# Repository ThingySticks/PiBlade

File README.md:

# Pi Blade

A 2U high "Blade" center for the Raspberry Pi (or many).

Design inspired by (1) which was inspired by (2) to use the DAP Audio 2 HE Rackblende f. Modulsystem 10 Segmente MP-1 (3), a 2U rack mount system with 10x 44mm wide panels.

## Rack Enclosure

This is the main intended enclosure, if the DAP Audio one isn't available this might be useful, hopefully some add-on bits for the modulsystem as well.

This is made of a number of parts.

* PiRackfrontPanel.svg/dxf - this is a 2U high laser cuttable version of the DAP Audio 2 HE Rackblende f. Modulsystem 10 Segmente MP-1. If you can't get the rack or don't want to wait (or don't mind an acrylic version this might work...

* PiRackRearSide.stl - a 3D printable 1/3 enclosure (side panel). 
** Intended to to around the back of the laser cut panel (not sure how well it will work with the proper rack).
** Print 2x of these, one for each side, then the middle section, these screw to the back of the laser cut acrylic.

## Standalone Enclosure

When getting the Pi's ready you probably don't want to put them in the rack, so this little barn style enclosure allows the blade to be screwed into it to hold it. The Fusion 360 design is scalable to allow multiple units.

* PiBarn-1.stl - 1 blade high
* PiBarn-3.stl - 3 blades high

# Front Panels

These consist of 3D printed panels () and are screwed to the blades.

* McPiFace - is a PCB panel, this can be sent to a fab house such as OSH Park to nicly make the panels.
* Panels from https://www.thingiverse.com/thing:2759317 can also be used and mounted onto the "Blades"

# Blades

These are the carrier frames for the Pi's. Compatible with https://www.thingiverse.com/thing:2759317

* PiRackPiBase.stl - this is the basic Pi blade base.
* PiRackPiLongBase.stl - this will hold 2x Pi's back to back, or HAT base from the Pi Sandwich https://github.com/ThingySticks/PiHatSandwich
** Obviously network connectivity is an issue for the second rear pi when mounting 2x Pi's.

## References

(1) https://www.thingiverse.com/thing:2759317
(2) https://www.thingiverse.com/thing:1793758
(3) https://www.musicstore.de/en_GB/GBP/DAP-Audio-2-HE-Rackblende-f-Modulsystem-10-Segmente-MP-1/art-PAH0017160-000

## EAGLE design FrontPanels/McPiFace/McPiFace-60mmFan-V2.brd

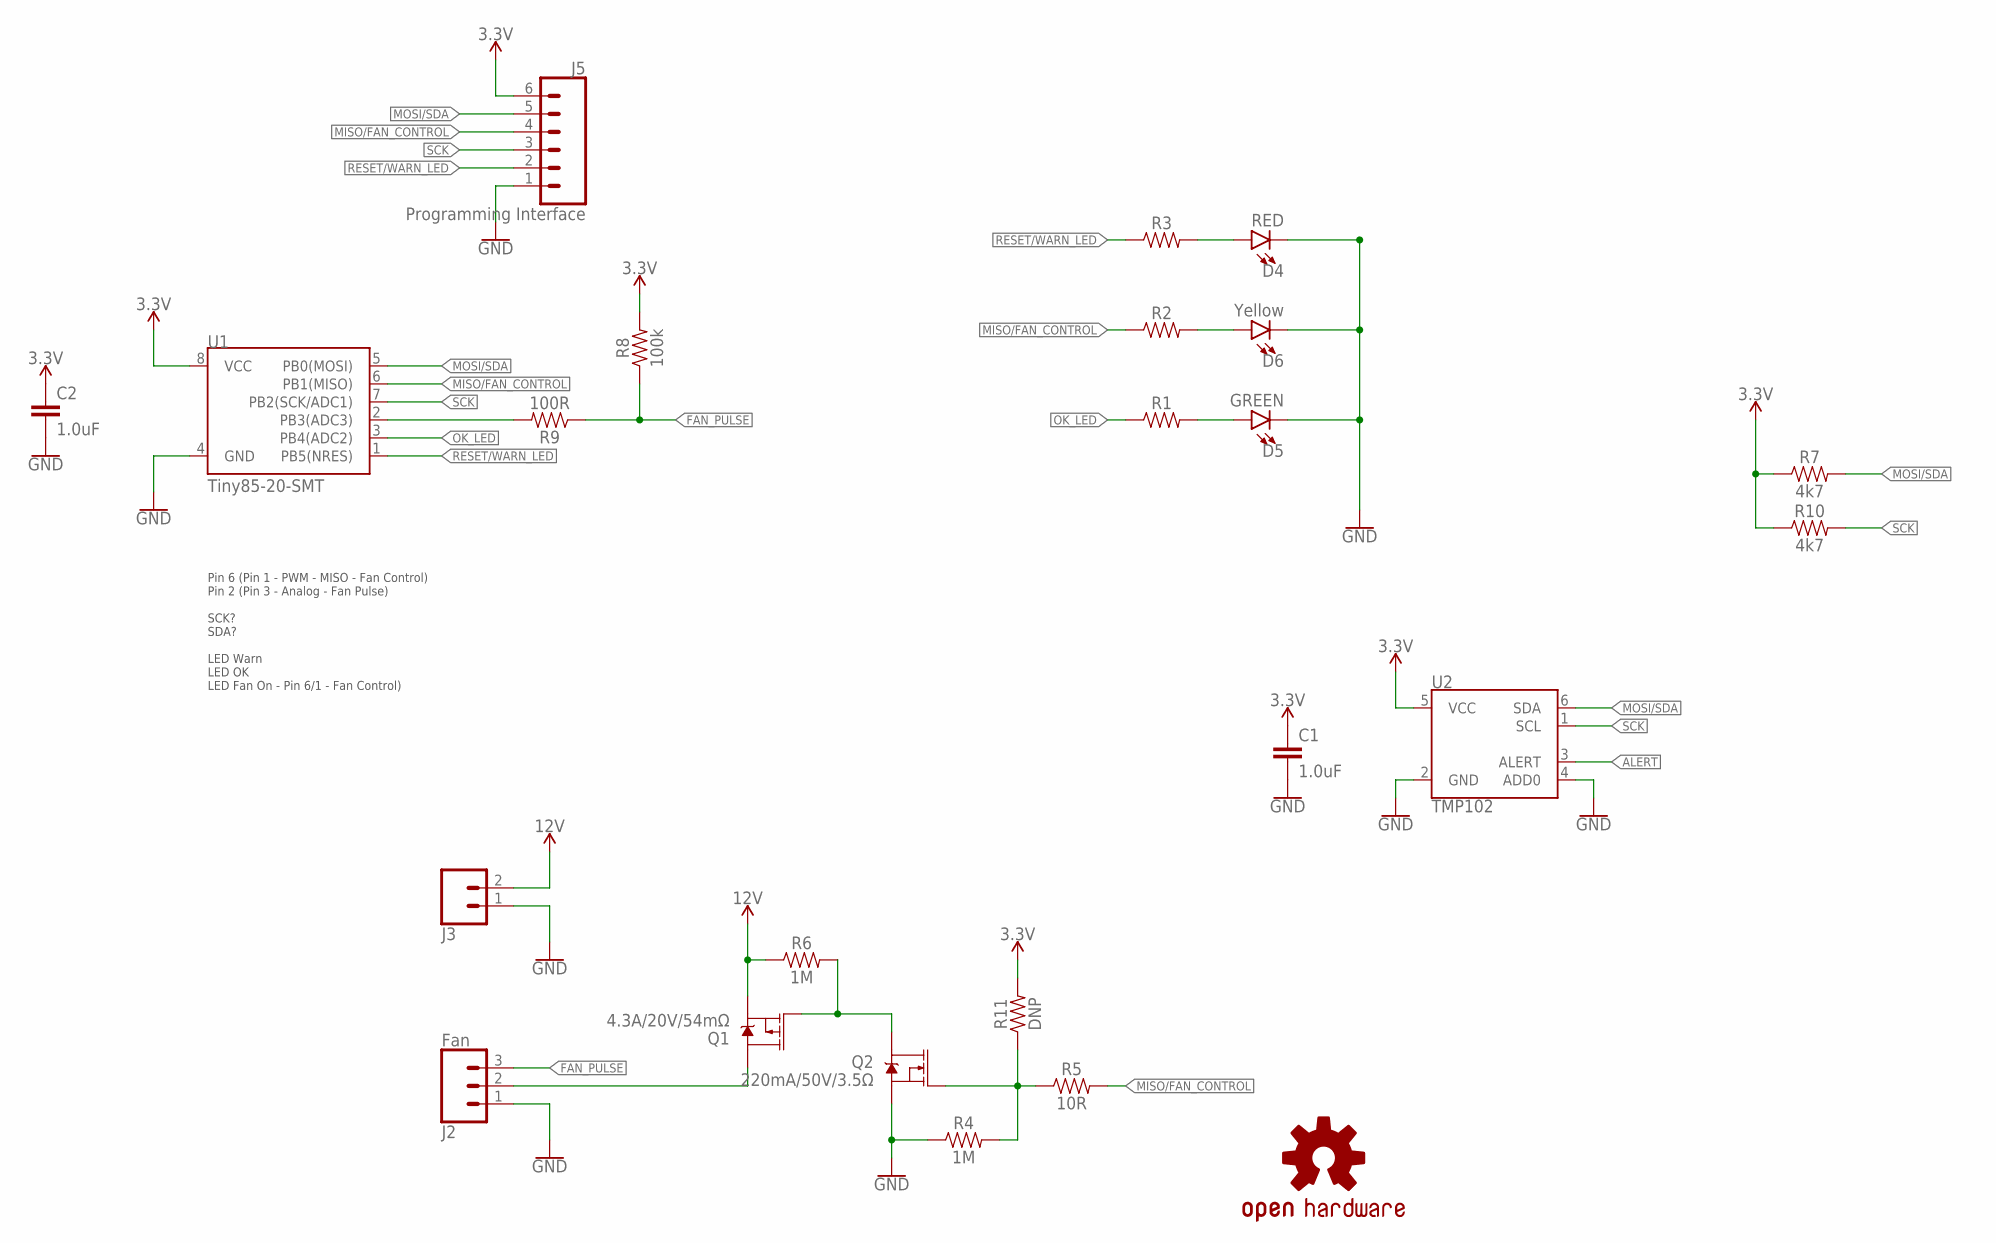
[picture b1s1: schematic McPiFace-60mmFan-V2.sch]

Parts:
C1, C2: 1.0uF; 0805
D4: RED; LED-1206
D5: GREEN; LED-1206
D6: Yellow; LED-1206
J2: Fan; JST-3-SMD; FARNELL 9492623
J3: CONN_02-JST-2MM-SMT; JST-2-SMD; FARNELL 9492615
J5: Programming Interface; 1X06-1MM
LOGO1: OSHW-LOGOL; OSHW-LOGO-L
Q1: 4.3A/20V/54mΩ; SOT23-3
Q2: 220mA/50V/3.5Ω; SOT23-3
R1, R2, R3: 1206
R4, R6: 1M; 0805
R5: 10R; 0805
R7, R10: 4k7; 0805
R8: 100k; 0805
R9: 100R; 0805
R11: DNP; 0805
U1: Tiny85-20-SMT; SO08-EIAJ
U2: TMP102; SOT563

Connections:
3.3V: C1.1, C2.1, J5.6, R7.1, R8.2, R10.1, R11.2, U1.8 (VCC), U2.5 (VCC)
12V: J3.2 (1), Q1.2 (S), R6.1
ALERT: U2.3 (ALERT)
FAN_PULSE: J2.3 (1), R8.1, R9.1
GND: C1.2, C2.2, D4.C, D5.C, D6.C, J2.1 (3), J3.1 (2), J5.1, Q2.2 (S), R4.1, U1.4 (GND), U2.2 (GND), U2.4 (ADD0)
MISO/FAN_CONTROL: J5.4, R2.1, R5.2, U1.6 (PB1(MISO))
MOSI/SDA: J5.5, R7.2, U1.5 (PB0(MOSI)), U2.6 (SDA)
unnamed: R9.2, U1.2 (PB3(ADC3))
unnamed: D4.A, R3.2
unnamed: D6.A, R2.2
unnamed: D5.A, R1.2
unnamed: J2.2, Q1.3 (D)
unnamed: Q1.1 (G), Q2.3 (D), R6.2
unnamed: Q2.1 (G), R4.2, R5.1, R11.1
OK_LED: R1.1, U1.3 (PB4(ADC2))
RESET/WARN_LED: J5.2, R3.1, U1.1 (PB5(NRES))
SCK: J5.3, R10.2, U1.7 (PB2(SCK/ADC1)), U2.1 (SCL)

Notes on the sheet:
Pin 6 (Pin 1 - PWM - MISO - Fan Control) Pin 2 (Pin 3 - Analog - Fan Pulse) SCK? SDA? LED Warn LED OK LED Fan On - Pin 6/1 - Fan Control)

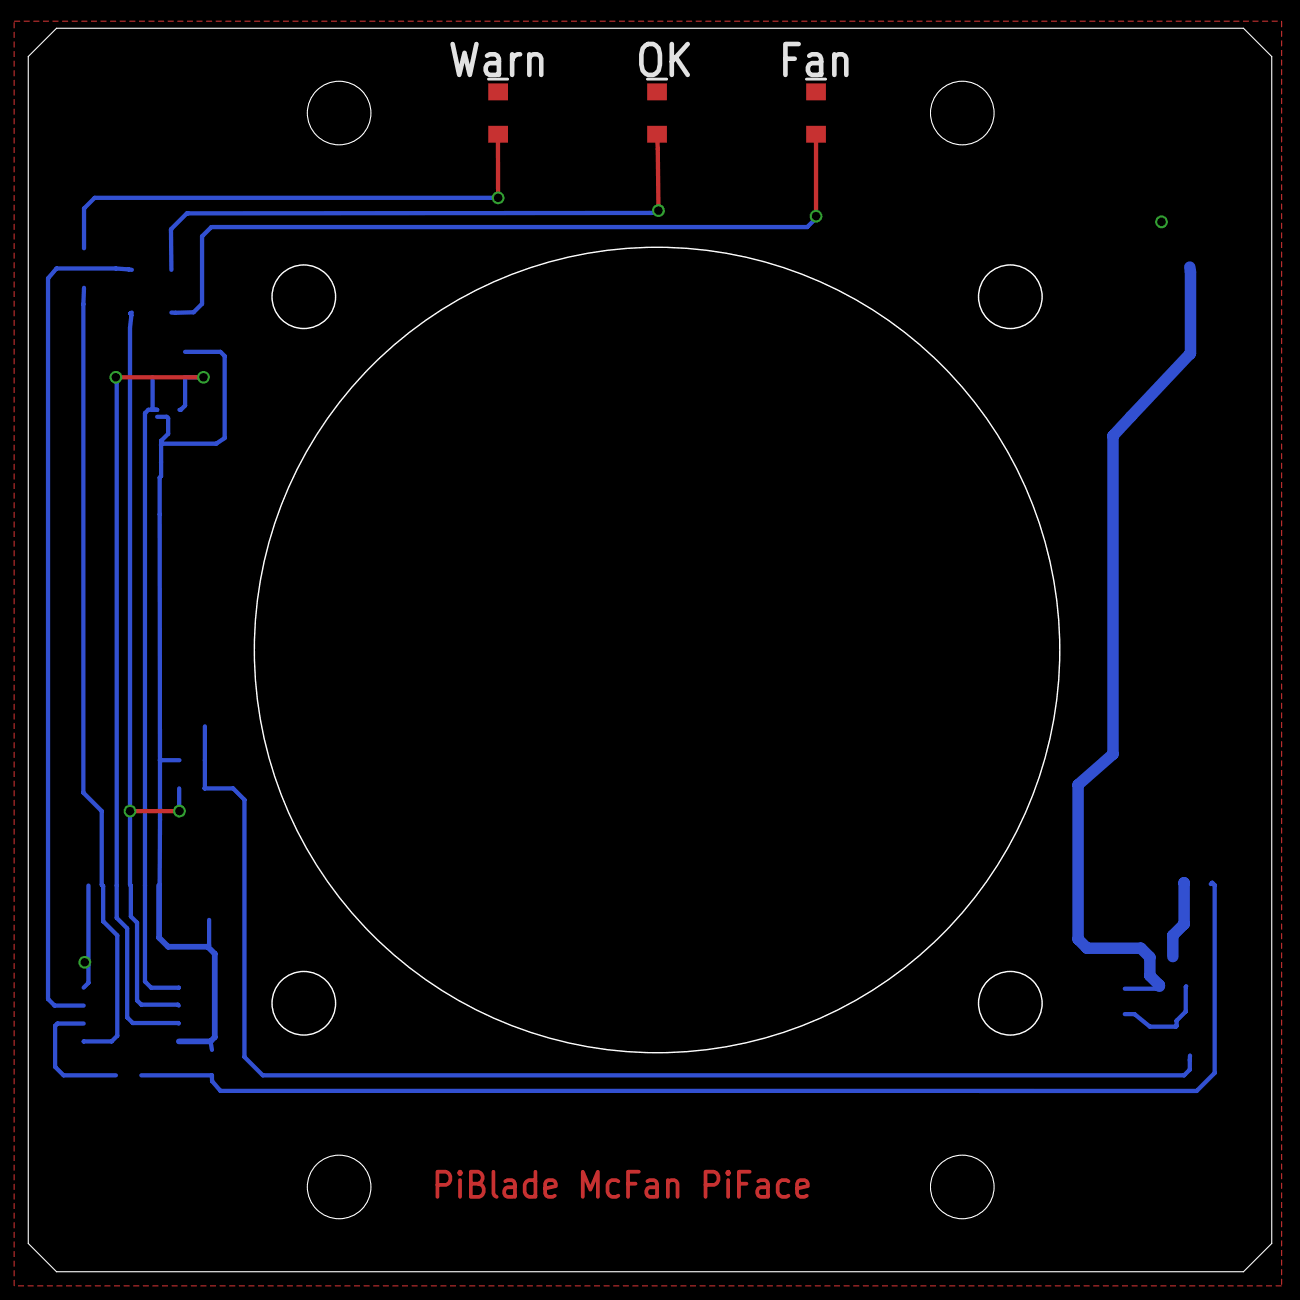
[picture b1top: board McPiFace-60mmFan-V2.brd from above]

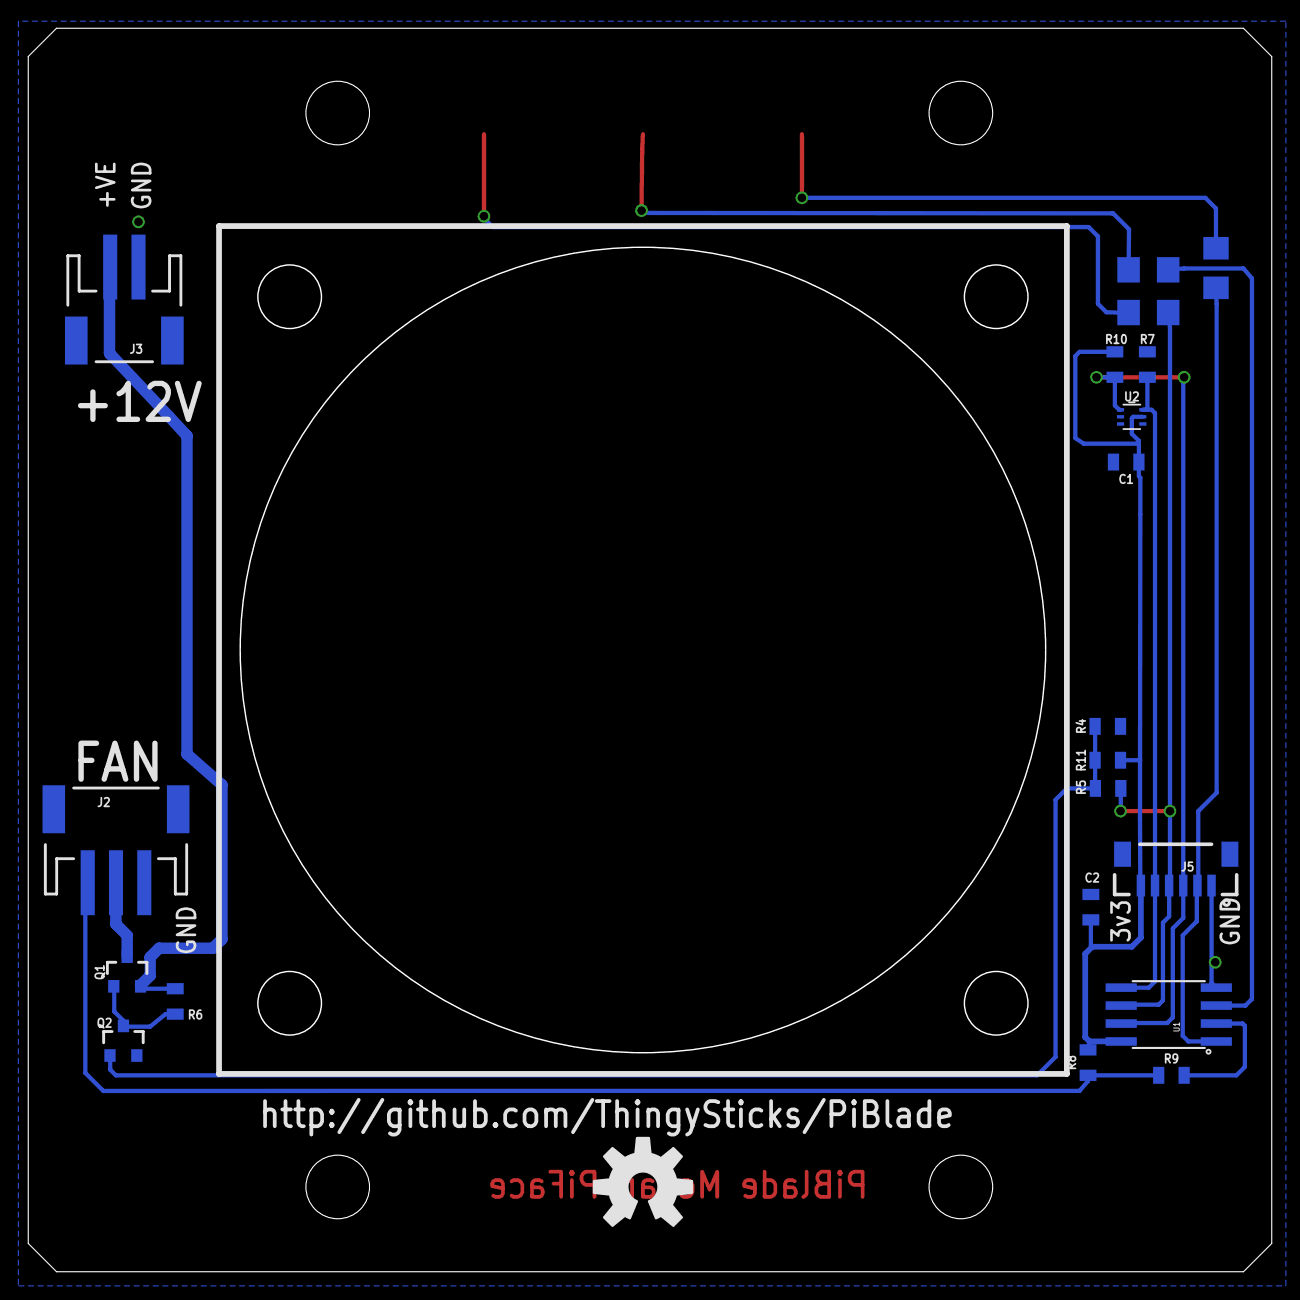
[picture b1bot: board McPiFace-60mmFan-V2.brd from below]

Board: 2 copper layers, 88.0 x 88.0 mm, 24 parts (21 on the bottom side), 16 nets.

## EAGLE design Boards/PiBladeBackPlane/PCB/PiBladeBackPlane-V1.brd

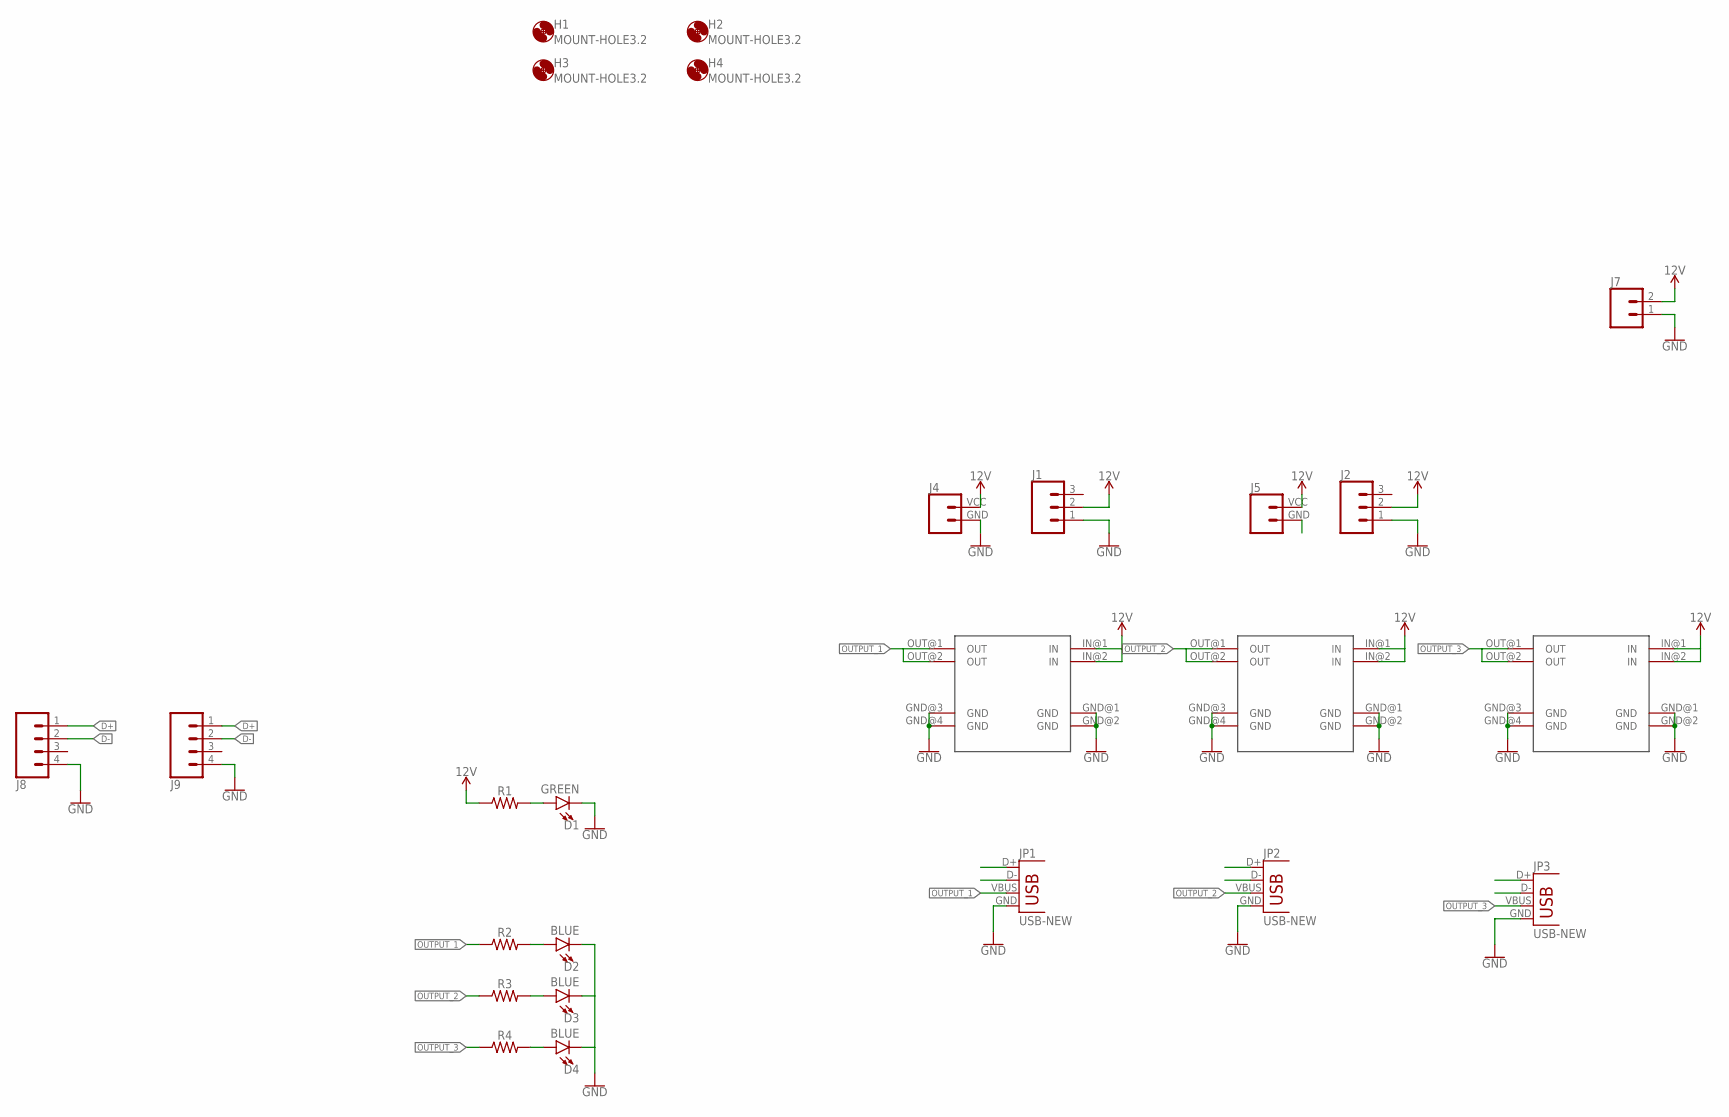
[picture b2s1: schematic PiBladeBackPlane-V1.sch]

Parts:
D1: GREEN; LED-1206
D2, D3, D4: BLUE; LED-1206
H1, H2, H3, H4: MOUNT-HOLE3.2; 3,2
J1, J2: CONN_03POLAR; MOLEX-1X3
J4, J5: CONN_024UCON-15767; JST-2-SMD-VERT
J7: CONN_025MM; SCREWTERMINAL-5MM-2
J8, J9: CONN_04JST-PTH-VERT; JST-4-PTH-VERT
JP1, JP2, JP3: USB-NEW; USB-A-VERTICAL
R1, R2, R3, R4: 1206
U$1, U$2, U$3: MINI-BUCK-MODULE-3A

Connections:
12V: J1.2, J2.2, J4.VCC (2), J5.VCC (2), J7.2, R1.1, U$1.IN@1 (IN), U$1.IN@2 (IN), U$2.IN@1 (IN), U$2.IN@2 (IN), U$3.IN@1 (IN), U$3.IN@2 (IN)
D+: J8.1, J9.1, JP1.D+, JP2.D+, JP3.D+
D-: J8.2, J9.2, JP1.D-, JP2.D-, JP3.D-
GND: D1.C, D2.C, D3.C, D4.C, J1.1, J2.1, J4.GND (1), J7.1, J8.4, JP1.GND, JP2.GND, JP3.GND, U$1.GND@1 (GND), U$1.GND@2 (GND), U$1.GND@3 (GND), U$1.GND@4 (GND), U$2.GND@1 (GND), U$2.GND@2 (GND), U$2.GND@3 (GND), U$2.GND@4 (GND), U$3.GND@1 (GND), U$3.GND@2 (GND), U$3.GND@3 (GND), U$3.GND@4 (GND)
unnamed: D1.A, R1.2
unnamed: D4.A, R4.2
unnamed: D2.A, R2.2
unnamed: D3.A, R3.2
OUTPUT_1: JP1.VBUS, R2.1, U$1.OUT@1 (OUT), U$1.OUT@2 (OUT)
OUTPUT_2: JP2.VBUS, R3.1, U$2.OUT@1 (OUT), U$2.OUT@2 (OUT)
OUTPUT_3: JP3.VBUS, R4.1, U$3.OUT@1 (OUT), U$3.OUT@2 (OUT)

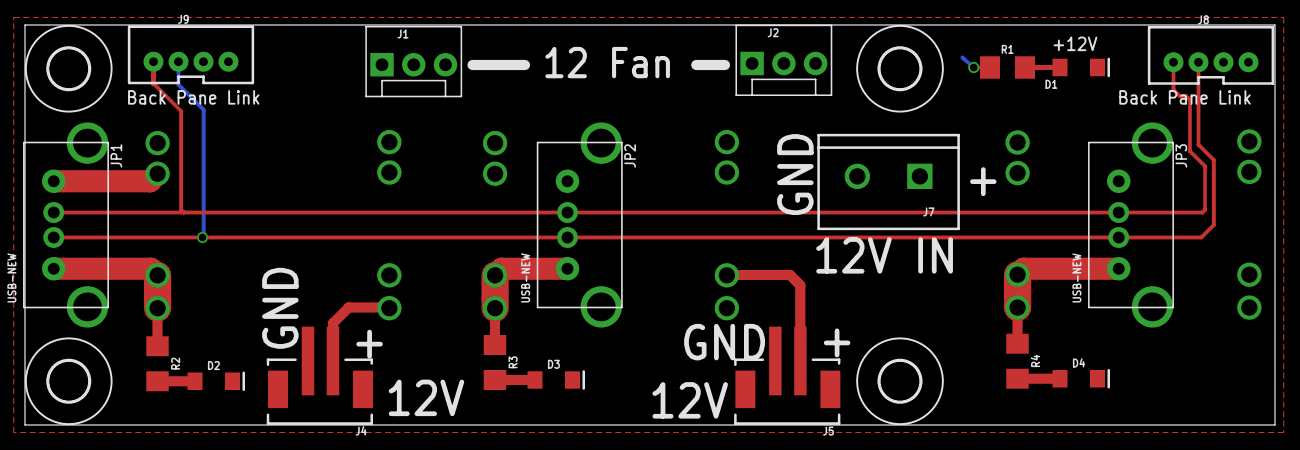
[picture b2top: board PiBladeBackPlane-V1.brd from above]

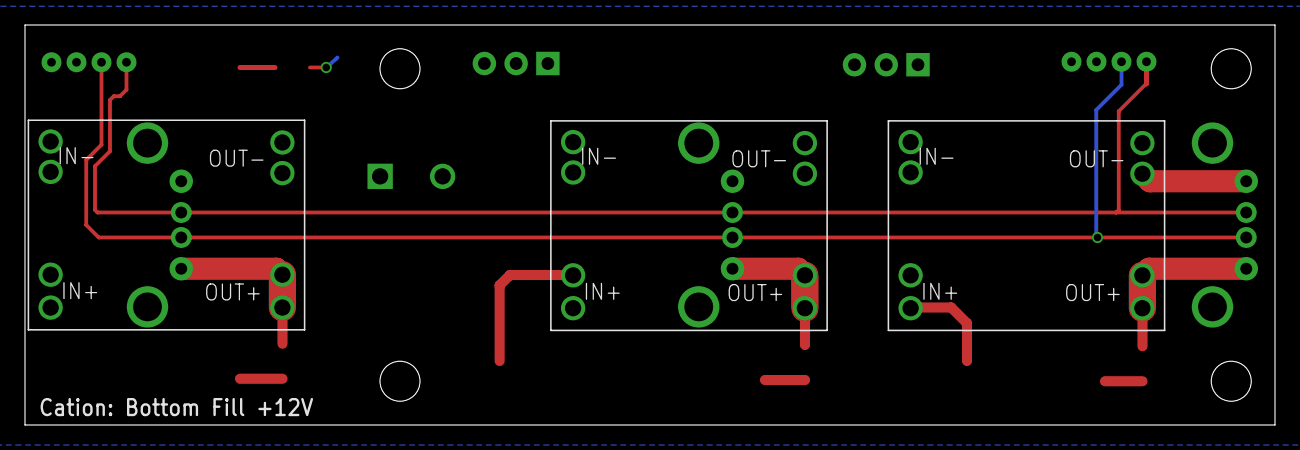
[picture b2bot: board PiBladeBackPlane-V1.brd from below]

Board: 2 copper layers, 100.0 x 32.0 mm, 25 parts (6 on the bottom side), 11 nets.

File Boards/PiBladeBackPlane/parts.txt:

Partlist

Exported from PiBladeBackPlane-V1.brd at 25/01/2019 11:45

EAGLE Version 7.4.0 Copyright (c) 1988-2015 CadSoft

Assembly variant: 

Part     Value               Package             Library             Position (mm)         Orientation

D1       GREEN               LED-1206            SparkFun-LED        (84.3 28.6)           R0
D2       BLUE                LED-1206            SparkFun-LED        (15.1 3.5)            R0
D3       BLUE                LED-1206            SparkFun-LED        (42.3 3.6)            R0
D4       BLUE                LED-1206            SparkFun-LED        (84.3 3.7)            R0
J1                           MOLEX-1X3           SparkFun-Connectors (28.56 28.82)         R0
J2                           MOLEX-1X3           SparkFun-Connectors (58.17 28.92)         R0
J4                           JST-2-SMD-VERT      SparkFun-Connectors (23.64 3.12)          R180
J5                           JST-2-SMD-VERT      SparkFun-Connectors (61.03 3.12)          R180
J7                           SCREWTERMINAL-5MM-2 SparkFun-Connectors (71.59 19.89)         R180
J8                           JST-4-PTH-VERT      SparkFun-Connectors (94.88 29.57)         R0
J9                           JST-4-PTH-VERT      SparkFun-Connectors (13.28 29.61)         R0
JP1      USB-NEW             USB-A-VERTICAL      Tinamous            (5 16)                MR0
JP2      USB-NEW             USB-A-VERTICAL      Tinamous            (46.1 16)             MR0
JP3      USB-NEW             USB-A-VERTICAL      Tinamous            (90.2 16)             MR0
R1                           1206                SparkFun-Resistors  (78.6 28.6)           R0
R2                           1206                SparkFun-Resistors  (10.6 4.9)            R270
R3                           1206                SparkFun-Resistors  (37.6 5)              R270
R4                           1206                SparkFun-Resistors  (79.4 5.1)            R270
U$1      MINI-BUCK-MODULE-3A MINI-BUCK-MODULE-3A Tinamous            (8.83 24.33)          MR180
U$2      MINI-BUCK-MODULE-3A MINI-BUCK-MODULE-3A Tinamous            (35.83 24.33)         MR180
U$3      MINI-BUCK-MODULE-3A MINI-BUCK-MODULE-3A Tinamous            (77.63 24.38)         MR180

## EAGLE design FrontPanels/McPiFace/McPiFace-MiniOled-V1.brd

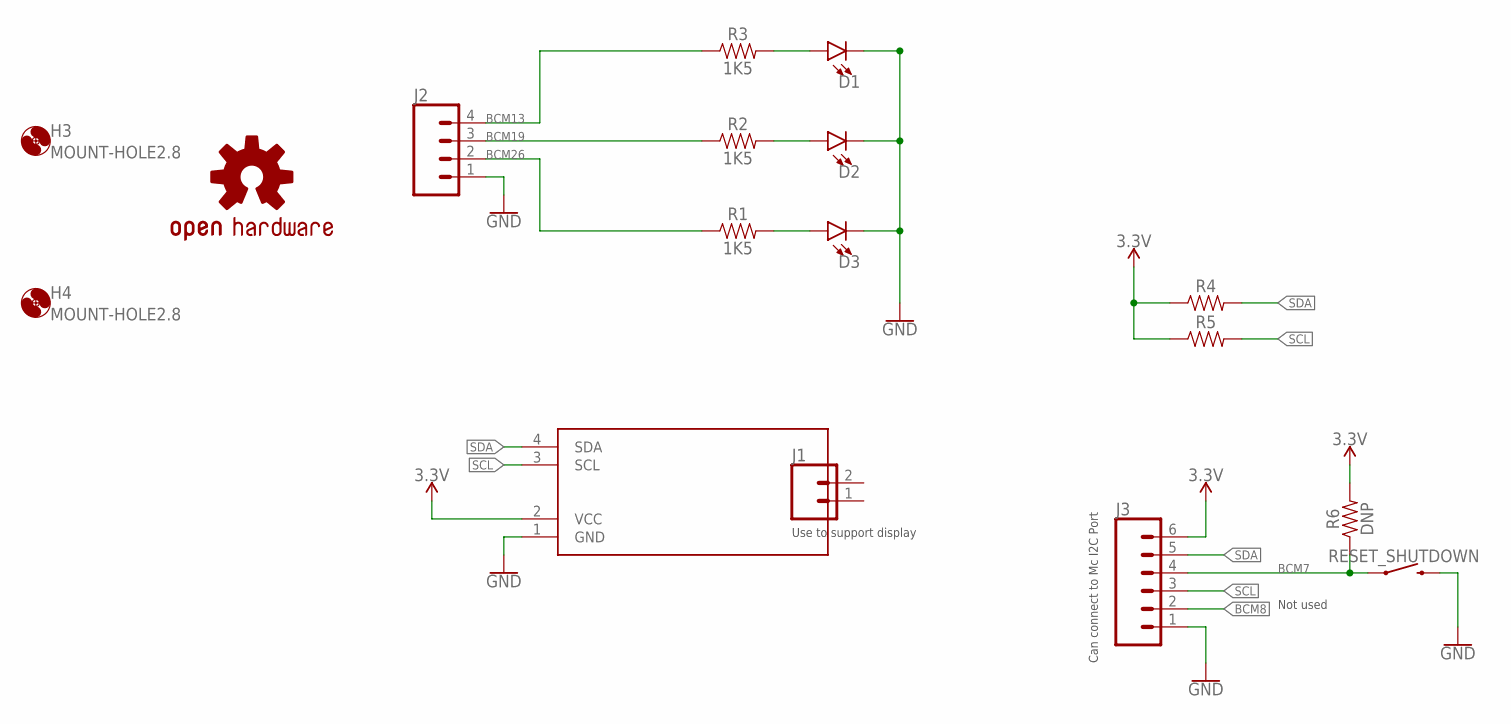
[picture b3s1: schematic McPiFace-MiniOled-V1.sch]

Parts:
D1, D2, D3: LED1206-BOTTOM-1.6MM; LED-1206-BOTTOM-1.6MM
DISPLAY: DISPLAY0.91_INCH_DISPLAY; I2C_DISPLAY_0.91_INCH
H3, H4: MOUNT-HOLE2.8; 2,8
J1: CONN_021X02_NO_SILK; 1X02_NO_SILK
J2: CONN_04SMD2; 1X04_1MM_RA
J3: CONN_06SMD-1MM; 1X06-1MM
LOGO1: OSHW-LOGOL; OSHW-LOGO-L
R1, R2, R3: 1K5; 0805
R4, R5: 0805
R6: DNP; 0805
RESET_SHUTDOWN: Reset/Powerdown; TACTILE_SWITCH_PTH_6.0MM_NO_TOP_RESIST

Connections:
3.3V: DISPLAY.2 (VCC), J3.6, R4.1, R5.1, R6.2
BCM7: J3.4, R6.1, RESET_SHUTDOWN.1
BCM8: J3.2
BCM13: J2.4, R3.1
BCM19: J2.3, R2.1
BCM26: J2.2, R1.1
GND: D1.C, D2.C, D3.C, DISPLAY.1 (GND), J2.1, J3.1, RESET_SHUTDOWN.3 (2)
unnamed: D3.A, R1.2
unnamed: D1.A, R3.2
unnamed: D2.A, R2.2
SCL: DISPLAY.3 (SCL), J3.3, R5.2
SDA: DISPLAY.4 (SDA), J3.5, R4.2

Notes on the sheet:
Use to support display
Not used
Can connect to Mc I2C Port

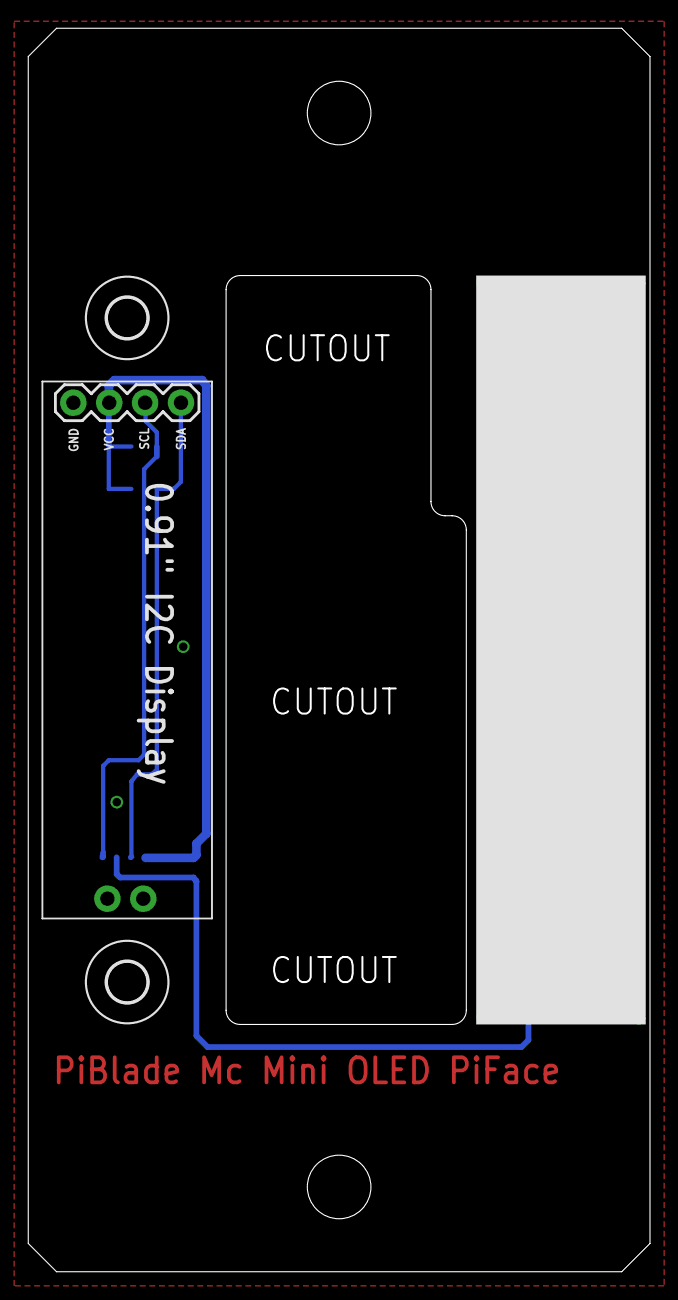
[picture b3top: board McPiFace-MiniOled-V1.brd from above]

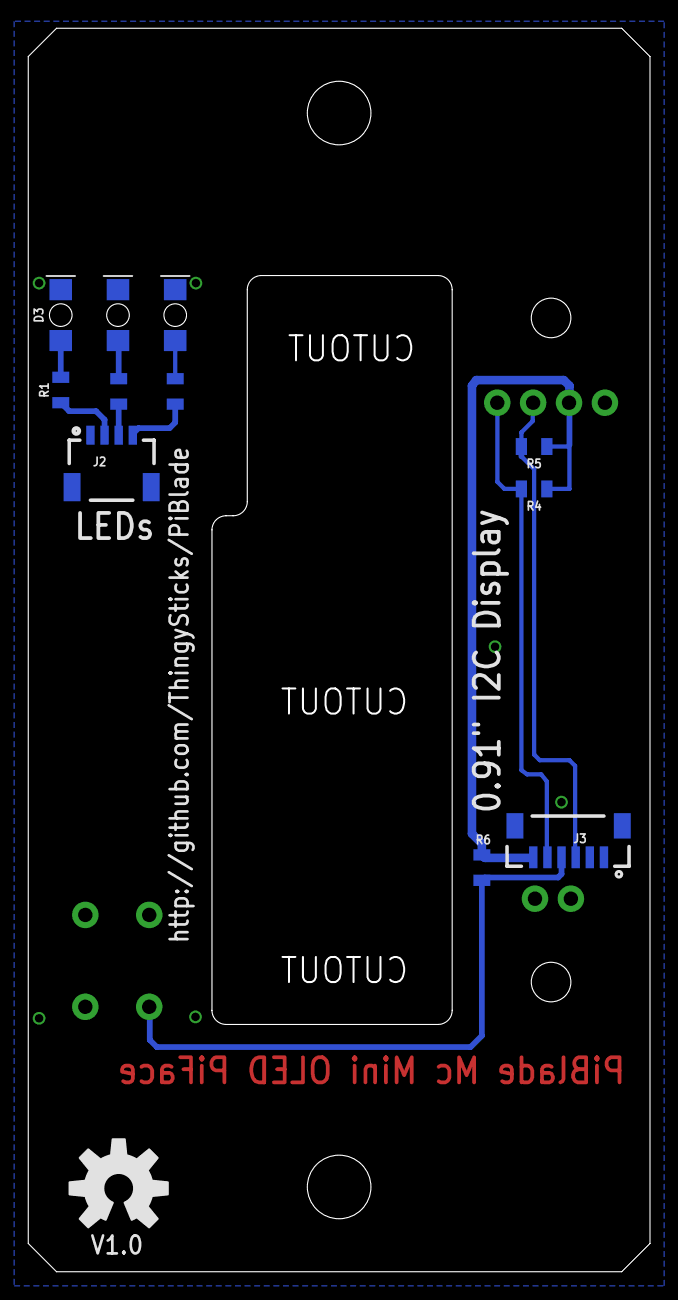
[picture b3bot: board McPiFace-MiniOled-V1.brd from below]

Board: 2 copper layers, 44.0 x 88.0 mm, 17 parts (12 on the bottom side), 11 nets.

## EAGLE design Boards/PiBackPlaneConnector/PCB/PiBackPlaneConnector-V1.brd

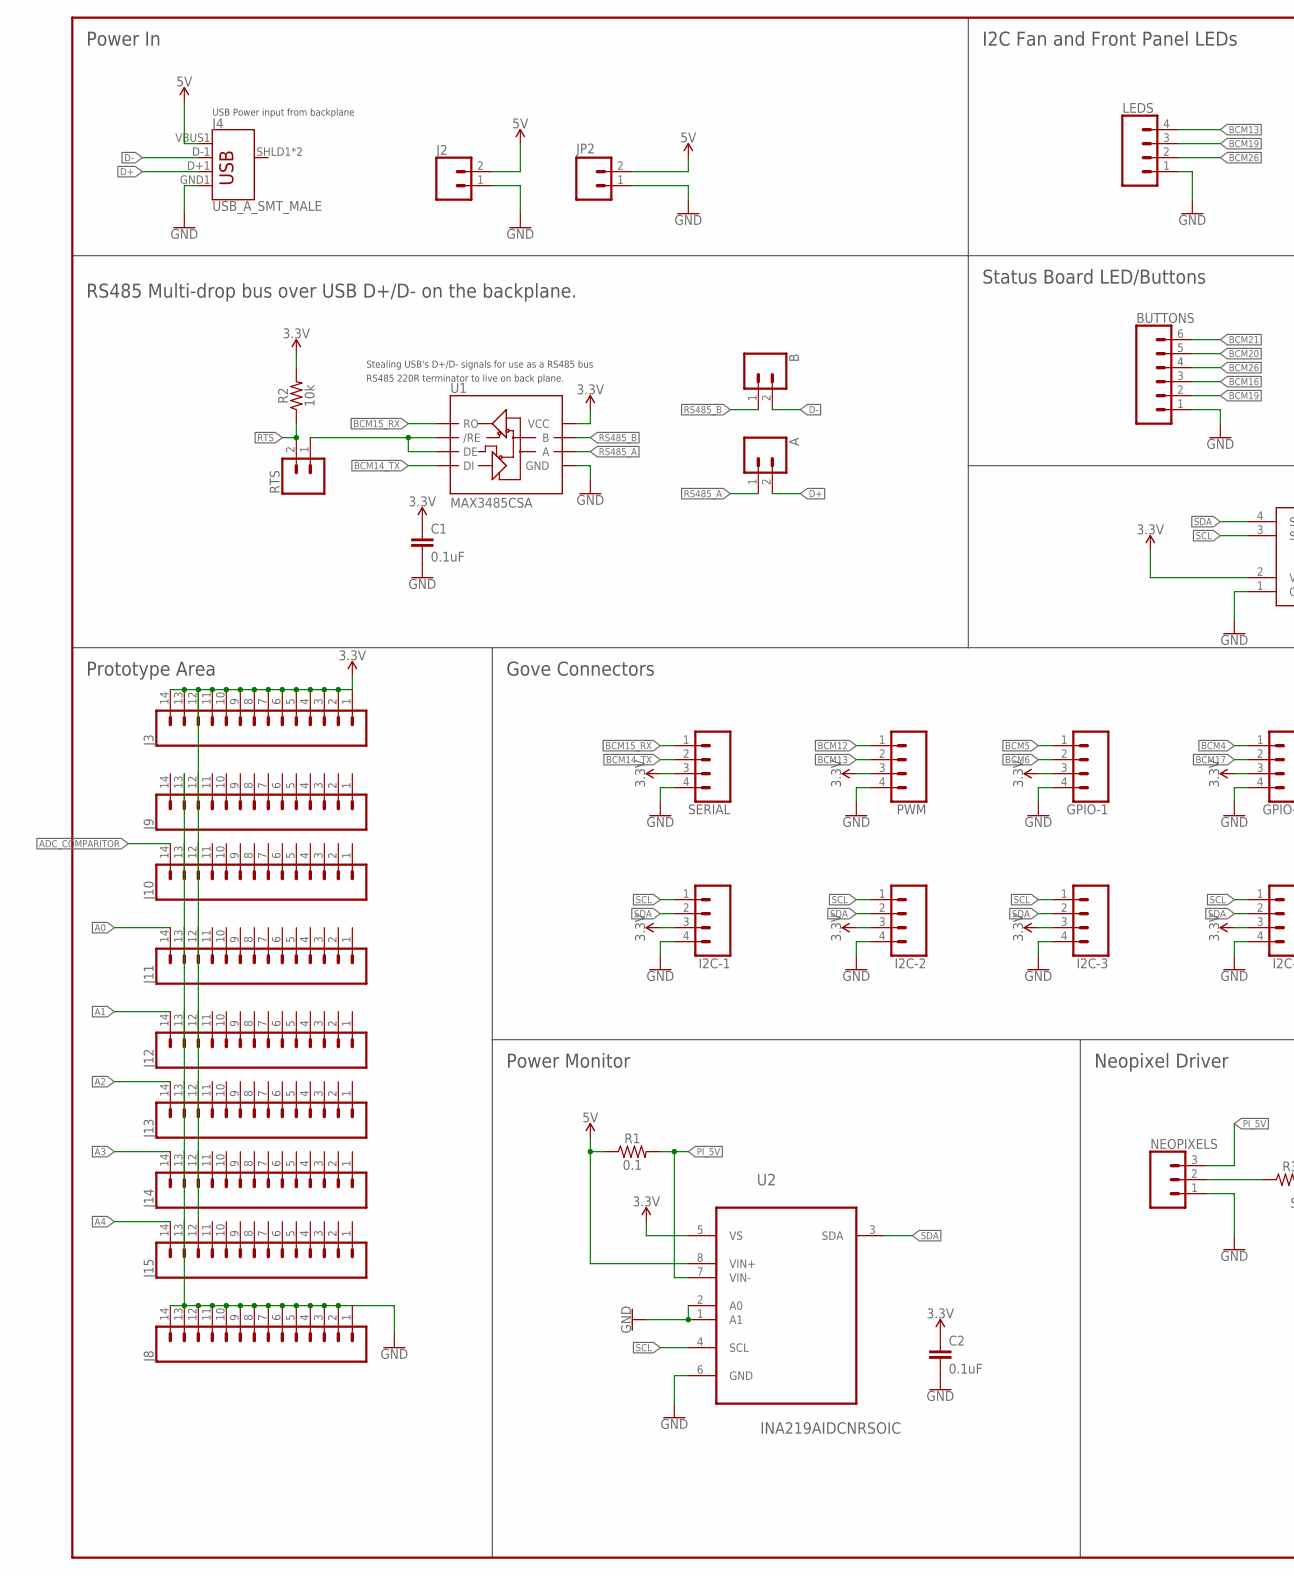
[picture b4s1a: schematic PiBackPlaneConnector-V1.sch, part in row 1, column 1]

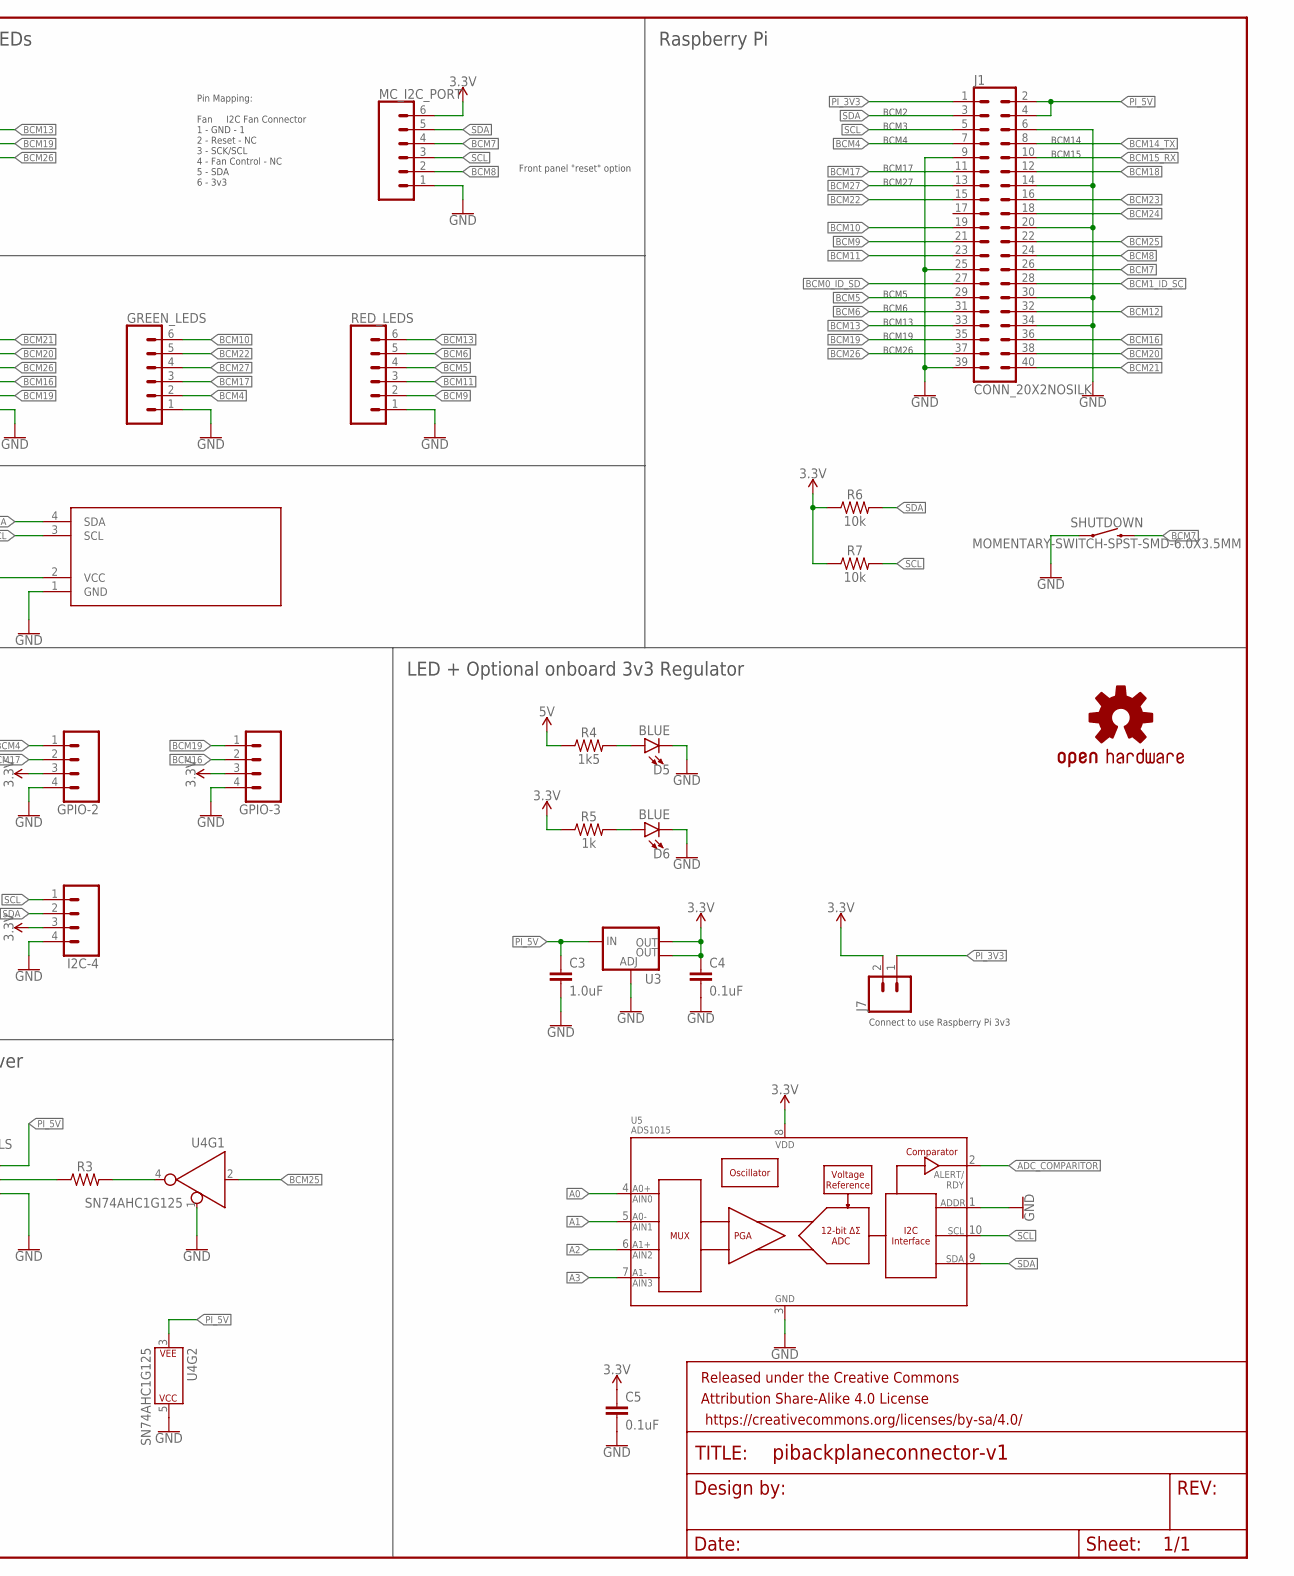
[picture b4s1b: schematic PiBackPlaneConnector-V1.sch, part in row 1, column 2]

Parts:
A: CONN_02; 1X02
B: CONN_02; 1X02
BUTTONS: CONN_06SMD-1MM; 1X06-1MM
C1, C2, C4, C5: 0.1uF; 0805
C3: 1.0uF; 0805
D5, D6: BLUE; LED-1206
DISPLAY: DISPLAY0.91_INCH_DISPLAY; I2C_DISPLAY_0.91_INCH
FRAME1: FRAME-LEDGER; CREATIVE_COMMONS
GPIO-1, GPIO-2, GPIO-3: CONN_04JST-PTH-VERT; JST-4-PTH-VERT
GREEN_LEDS: CONN_06SMD-1MM; 1X06-1MM
I2C-1, I2C-2, I2C-3, I2C-4: CONN_04JST-PTH-VERT; JST-4-PTH-VERT
J1: CONN_20X2NOSILK; 2X20_NOSILK
J2: CONN_02POLAR; MOLEX-1X2
J3, J8: CONN_14; 1X14
J4: USB_A_SMT_MALE; USB-A-SMT-MALE
J7: CONN_02; 1X02
J9, J10, J11, J12, J13, J14, J15: CONN_14NO_SILK; 1X14_NO_SILK
JP2: M025MM; SCREWTERMINAL-5MM-2@1
LEDS: CONN_04SMD2; 1X04_1MM_RA
LOGO1: OSHW-LOGOM; OSHW-LOGO-M
MC_I2C_PORT: CONN_06SMD-1MM; 1X06-1MM
NEOPIXELS: CONN_03POLAR; MOLEX-1X3
PWM: CONN_04JST-PTH-VERT; JST-4-PTH-VERT
R1: 0.1; 1210
R2, R6, R7: 10k; 0805
R3: 0805
R4: 1k5; 0805
R5: 1k; 0805
RED_LEDS: CONN_06SMD-1MM; 1X06-1MM
RTS: CONN_02; 1X02
SERIAL: CONN_04JST-PTH-VERT; JST-4-PTH-VERT
SHUTDOWN: MOMENTARY-SWITCH-SPST-SMD-6.0X3.5MM; TACTILE_SWITCH_SMD_6.0X3.5MM
U1: MAX3485CSA; SO08
U2: INA219AIDCNRSOIC; SO08
U3: V_REG_LM1117SOT223; SOT223
U4: SN74AHC1G125; SOT23-5
U5: ADS1015; MSOP10

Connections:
3.3V: C1.1, C2.1, C4.1, C5.1, DISPLAY.2 (VCC), GPIO-1.3, GPIO-2.3, GPIO-3.3, I2C-1.3, I2C-2.3, I2C-3.3, I2C-4.3, J3.1, J3.2, J3.3, J3.4, J3.5, J3.6, J3.7, J3.8, J3.9, J3.10, J3.11, J3.12, J3.13, J3.14, J7.2, J9.12, J10.12, J11.12, J12.12, J13.12, J14.12, J15.12, MC_I2C_PORT.6, PWM.3, R2.2, R5.1, R6.1, R7.1, SERIAL.3, U1.8 (VCC), U2.5 (VS), U3.2 (OUT), U3.4 (OUT), U5.8 (VDD)
5V: J2.2, J4.VBUS1 (VBUS), JP2.2, R1.1, R4.1, U2.8 (VIN+)
A0: J11.14, U5.4 (AIN0)
A1: J12.14, U5.5 (AIN1)
A2: J13.14, U5.6 (AIN2)
A3: J14.14, U5.7 (AIN3)
A4: J15.14
ADC_COMPARITOR: J10.14, U5.2 (ALERT/RDY)
BCM0_ID_SD: J1.27
BCM1_ID_SC: J1.28
BCM4: GPIO-2.1, GREEN_LEDS.2, J1.7
BCM5: GPIO-1.1, J1.29, RED_LEDS.4
BCM6: GPIO-1.2, J1.31, RED_LEDS.5
BCM7: J1.26, MC_I2C_PORT.4, SHUTDOWN.2
BCM8: J1.24, MC_I2C_PORT.2
BCM9: J1.21, RED_LEDS.2
BCM10: GREEN_LEDS.6, J1.19
BCM11: J1.23, RED_LEDS.3
BCM12: J1.32, PWM.1
BCM13: J1.33, LEDS.4, PWM.2, RED_LEDS.6
BCM14_TX: J1.8, SERIAL.2, U1.4 (DI)
BCM15_RX: J1.10, SERIAL.1, U1.1 (RO)
BCM16: BUTTONS.3, GPIO-3.2, J1.36
BCM17: GPIO-2.2, GREEN_LEDS.3, J1.11
BCM18: J1.12
BCM19: BUTTONS.2, GPIO-3.1, J1.35, LEDS.3
BCM20: BUTTONS.5, J1.38
BCM21: BUTTONS.6, J1.40
BCM22: GREEN_LEDS.5, J1.15
BCM23: J1.16
BCM24: J1.18
BCM25: J1.22, U4.2 (A)
BCM26: BUTTONS.4, J1.37, LEDS.2
BCM27: GREEN_LEDS.4, J1.13
D+: A.2, J4.D+1 (D+)
D-: B.2, J4.D-1 (D-)
GND: BUTTONS.1, C1.2, C2.2, C3.2, C4.2, C5.2, D5.C, D6.C, DISPLAY.1 (GND), GPIO-1.4, GPIO-2.4, GPIO-3.4, GREEN_LEDS.1, I2C-1.4, I2C-2.4, I2C-3.4, I2C-4.4, J1.6, J1.9, J1.14, J1.20, J1.25, J1.30, J1.34, J1.39, J2.1, J4.GND1 (GND), J8.1, J8.2, J8.3, J8.4, J8.5, J8.6, J8.7, J8.8, J8.9, J8.10, J8.11, J8.12, J8.13, J8.14, J9.13, J10.13, J11.13, J12.13, J13.13, J14.13, J15.13, JP2.1, LEDS.1, MC_I2C_PORT.1, NEOPIXELS.1, PWM.4, RED_LEDS.1, SERIAL.4, SHUTDOWN.1, U1.5 (GND), U2.1 (A1), U2.2 (A0), U2.6 (GND), U3.1 (ADJ), U4.1 (!EN), U4.5 (P$V+), U5.1 (ADDR), U5.3 (VSS)
unnamed: D6.A, R5.2
unnamed: D5.A, R4.2
unnamed: RTS.1, U1.2 (/RE), U1.3 (DE)
unnamed: NEOPIXELS.2, R3.1
unnamed: R3.2, U4.4 (Y)
PI_3V3: J1.1, J7.1
PI_5V: C3.1, J1.2, J1.4, NEOPIXELS.3, R1.2, U2.7 (VIN-), U3.3 (IN), U4.3 (P$V-)
RS485_A: A.1, U1.6 (A)
RS485_B: B.1, U1.7 (B)
RTS: R2.1, RTS.2
SCL: DISPLAY.3 (SCL), I2C-1.1, I2C-2.1, I2C-3.1, I2C-4.1, J1.5, MC_I2C_PORT.3, R7.2, U2.4 (SCL), U5.10 (SCL)
SDA: DISPLAY.4 (SDA), I2C-1.2, I2C-2.2, I2C-3.2, I2C-4.2, J1.3, MC_I2C_PORT.5, R6.2, U2.3 (SDA), U5.9 (SDA)

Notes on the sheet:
BCM13
BCM6
BCM5
BCM26
BCM19
Stealing USB's D+/D- signals for use as a RS485 bus
RS485 220R terminator to live on back plane.
Connect to use Raspberry Pi 3v3
USB Power input from backplane
BCM14
BCM15
BCM2
BCM3
BCM4
BCM17
BCM27
Pin Mapping: Fan I2C Fan Connector 1 - GND - 1 2 - Reset - NC 3 - SCK/SCL 4 - Fan Control - NC 5 - SDA 6 - 3v3
Power In
RS485 Multi-drop bus over USB D+/D- on the backplane.
Raspberry Pi
Prototype Area
Gove Connectors
LED + Optional onboard 3v3 Regulator
Status Board LED/Buttons
I2C Fan and Front Panel LEDs
Neopixel Driver
Power Monitor
Front panel "reset" option

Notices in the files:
parts and their libraries:
SparkFun-Connectors: Licensing: Creative Commons ShareAlike 4.0 International - https://creativecommons.org/licenses/by-sa/4.0
SparkFun-Aesthetics: Released under the Creative Commons Attribution Share-Alike 4.0 License
SparkFun-Aesthetics: https://creativecommons.org/licenses/by-sa/4.0
